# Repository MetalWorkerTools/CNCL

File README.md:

# CNCL
[CNCL](https://www.microsoft.com/store/apps/9P42TB5T697H), a conversational lathe application, gives a CNC controlled conventional lathe the ability to perform CNC tasks without CNC programming or the need for a CAD or CAM program. [CNCL](https://www.microsoft.com/store/apps/9P42TB5T697H) makes it easy to precisely turn a radius or a taper, grind drills and mills, broach a gear, knurl (cut) a shaft, do any pitch (high precision) threading or rigid tapping, turn a spur gear or pulley cutter, mill a helix gear, simply by setting a few parameters. No complex calculations needed, all you need are the dimensions of the part to turn. The built-in tool change and tool library let you select a tool and continue without the need for adjusting positions. Change from Metric to Inches by a click on a button. Backlash compensation is implemented, no need to fit ball screws. For repetitive tasks, a record and play-back function is available. The recorded GCodes can be saved for use on other types of controllers. A manual is built-in and can be printed.  
[CNCL](https://www.microsoft.com/store/apps/9P42TB5T697H) is optimized to run on a small 10" touch screen (tablet). The supported controllers are [GRBL](https://github.com/gnea/grbl/wiki), [GRBL-L](https://github.com/MetalWorkerTools/grbl-L), [GRBL-L-Mega](https://github.com/MetalWorkerTools/grbl-L-Mega),  [uCNC](https://github.com/Paciente8159/uCNC/wiki), [grblHAL](https://github.com/grblHAL/core/wiki), [FluidNC](http://wiki.fluidnc.com/en/home), [Grbl_ESP32](https://github.com/bdring/Grbl_Esp32/wiki) or compatibles, free open source controllers based on affordable (Arduino) hardware. Check the [hardware compatibility list](https://github.com/MetalWorkerTools/CNCL/wiki/Hardware-Compatibility-List) for more information. The controller can be connected by USB, Bluetooth or a (Wi-Fi) network.  
If you ever wanted to start with CNC, this is the easy and affordable way to do it.
[CNCL](https://www.microsoft.com/store/apps/9P42TB5T697H) is also provided as a 30 days trial version. The trial version is a full version without limitations. Check the License Information task for more information.  
[CNCL](https://www.microsoft.com/store/apps/9P42TB5T697H) is available from the Microsoft Store.  

Thinking about a CNC rotary table, checkout [CNCR](https://www.microsoft.com/store/apps/9N7HPG47XK0G) from the Microsoft store..
<p>&nbsp;</p> 

## For more information, read the [WiKi](https://github.com/MetalWorkerTools/CNCL/wiki)
## Version [2.4.1](https://github.com/MetalWorkerTools/CNCL/wiki/Version-Information) is released on 10-2026.
## Use [**Issues**](https://github.com/MetalWorkerTools/CNCL/issues) to report a bug or request a feature

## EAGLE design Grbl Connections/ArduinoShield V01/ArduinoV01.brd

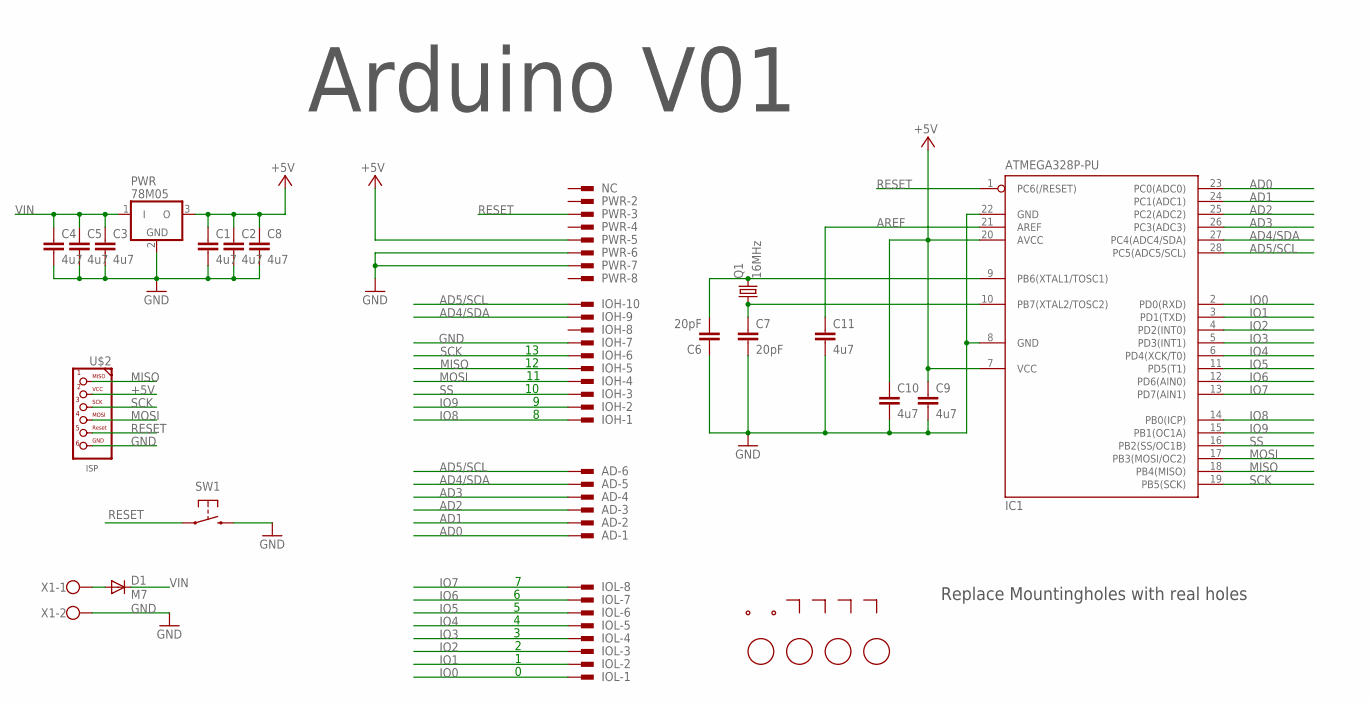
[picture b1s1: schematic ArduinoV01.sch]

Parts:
AD-1, AD-2, AD-3, AD-4, AD-5, AD-6: PINHD-1X1; 1X01
C1, C2, C3, C4, C5, C8, C9, C10, C11: 4u7; C0805
C6, C7: 20pF; C0805
D1: M7; DO214AC
FD1, FD2, FD3, FD4: FIDUCIALMOUNT; FIDUCIA-MOUNT
IC1: ATMEGA328P-PU; DIL28-3
IOH-1, IOH-2, IOH-3, IOH-4, IOH-5, IOH-6, IOH-7, IOH-8, IOH-9, IOH-10: PINHD-1X1; 1X01
IOL-1, IOL-2, IOL-3, IOL-4, IOL-5, IOL-6, IOL-7, IOL-8: PINHD-1X1; 1X01
NC: PINHD-1X1; 1X01
PWR: 78M05; DPACK
PWR-2, PWR-3, PWR-4, PWR-5, PWR-6, PWR-7, PWR-8: PINHD-1X1; 1X01
Q1: 16MHz; HC49/S
SW1: SWITCH1X2; SW8X4-SMD
U$1: MARKERDUAL-90; MARKER90
U$2: ISPE; 2X03EDGE
U$3, U$4, U$5, U$6: MARKER
X1: SCREWTERMINATOR1X2V; W237-102V

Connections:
+5V: C1.1, C2.1, C8.1, C9.1, C10.1, IC1.7 (VCC), IC1.20 (AVCC), PWR.3 (O), PWR-5.1, U$2.P$2 (2)
AD0: AD-1.1, IC1.23 (PC0(ADC0))
AD1: AD-2.1, IC1.24 (PC1(ADC1))
AD2: AD-3.1, IC1.25 (PC2(ADC2))
AD3: AD-4.1, IC1.26 (PC3(ADC3))
AD4/SDA: AD-5.1, IC1.27 (PC4(ADC4/SDA)), IOH-9.1
AD5/SCL: AD-6.1, IC1.28 (PC5(ADC5/SCL)), IOH-10.1
AREF: C11.1, IC1.21 (AREF)
GND: C1.2, C2.2, C3.2, C4.2, C5.2, C6.1, C7.2, C8.2, C9.2, C10.2, C11.2, IC1.8 (GND), IC1.22 (GND), IOH-7.1, PWR.2 (GND), PWR-6.1, PWR-7.1, SW1.2 (S), U$2.P$6 (6), X1.2
IO0: IC1.2 (PD0(RXD)), IOL-1.1
IO1: IC1.3 (PD1(TXD)), IOL-2.1
IO2: IC1.4 (PD2(INT0)), IOL-3.1
IO3: IC1.5 (PD3(INT1)), IOL-4.1
IO4: IC1.6 (PD4(XCK/T0)), IOL-5.1
IO5: IC1.11 (PD5(T1)), IOL-6.1
IO6: IC1.12 (PD6(AIN0)), IOL-7.1
IO7: IC1.13 (PD7(AIN1)), IOL-8.1
IO8: IC1.14 (PB0(ICP)), IOH-1.1
IO9: IC1.15 (PB1(OC1A)), IOH-2.1
MISO: IC1.18 (PB4(MISO)), IOH-5.1, U$2.P$1 (1)
MOSI: IC1.17 (PB3(MOSI/OC2)), IOH-4.1, U$2.P$4 (4)
unnamed: C6.2, IC1.9 (PB6(XTAL1/TOSC1)), Q1.2
unnamed: C7.1, IC1.10 (PB7(XTAL2/TOSC2)), Q1.1
unnamed: D1.A, X1.1
RESET: IC1.1 (PC6(/RESET)), PWR-3.1, SW1.1, U$2.P$5 (5)
SCK: IC1.19 (PB5(SCK)), IOH-6.1, U$2.P$3 (3)
SS: IC1.16 (PB2(SS/OC1B)), IOH-3.1
VIN: C3.1, C4.1, C5.1, D1.C, PWR.1 (I)

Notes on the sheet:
Arduino V01
Replace Mountingholes with real holes

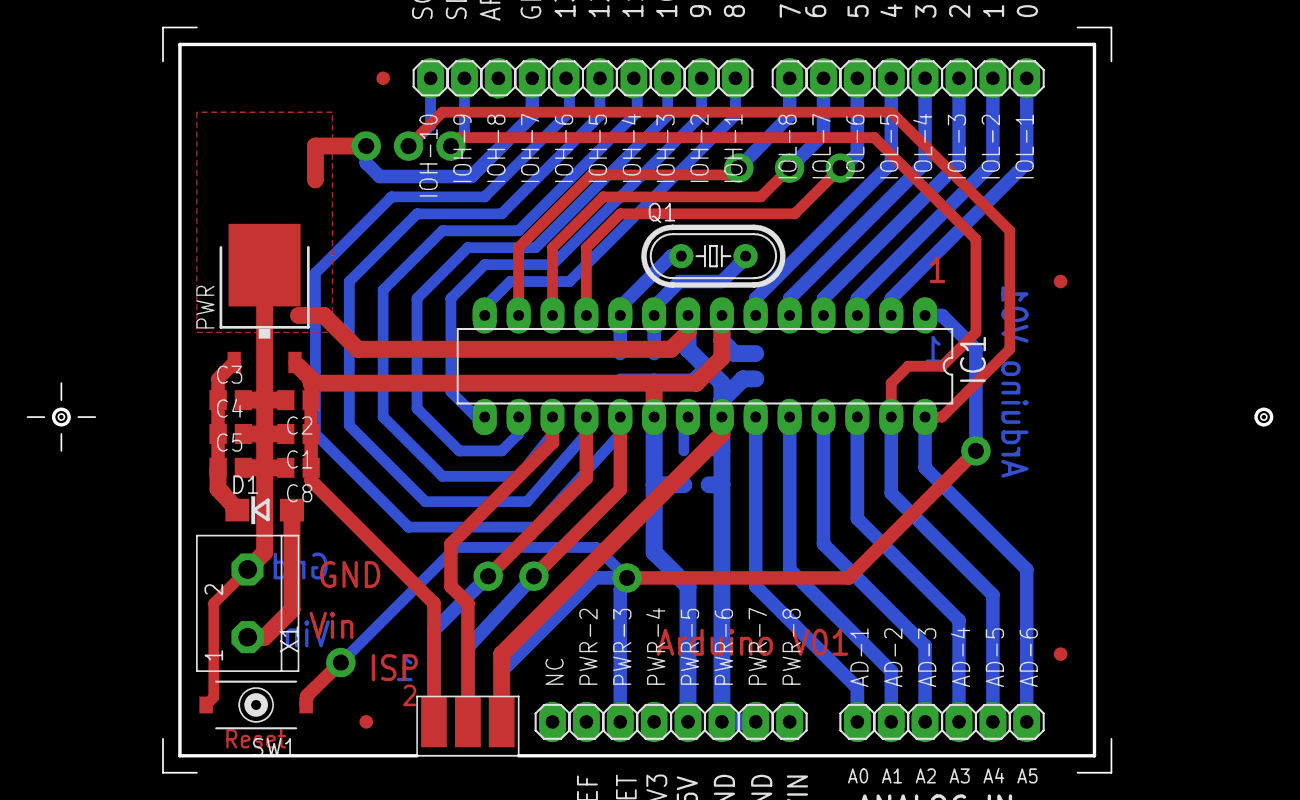
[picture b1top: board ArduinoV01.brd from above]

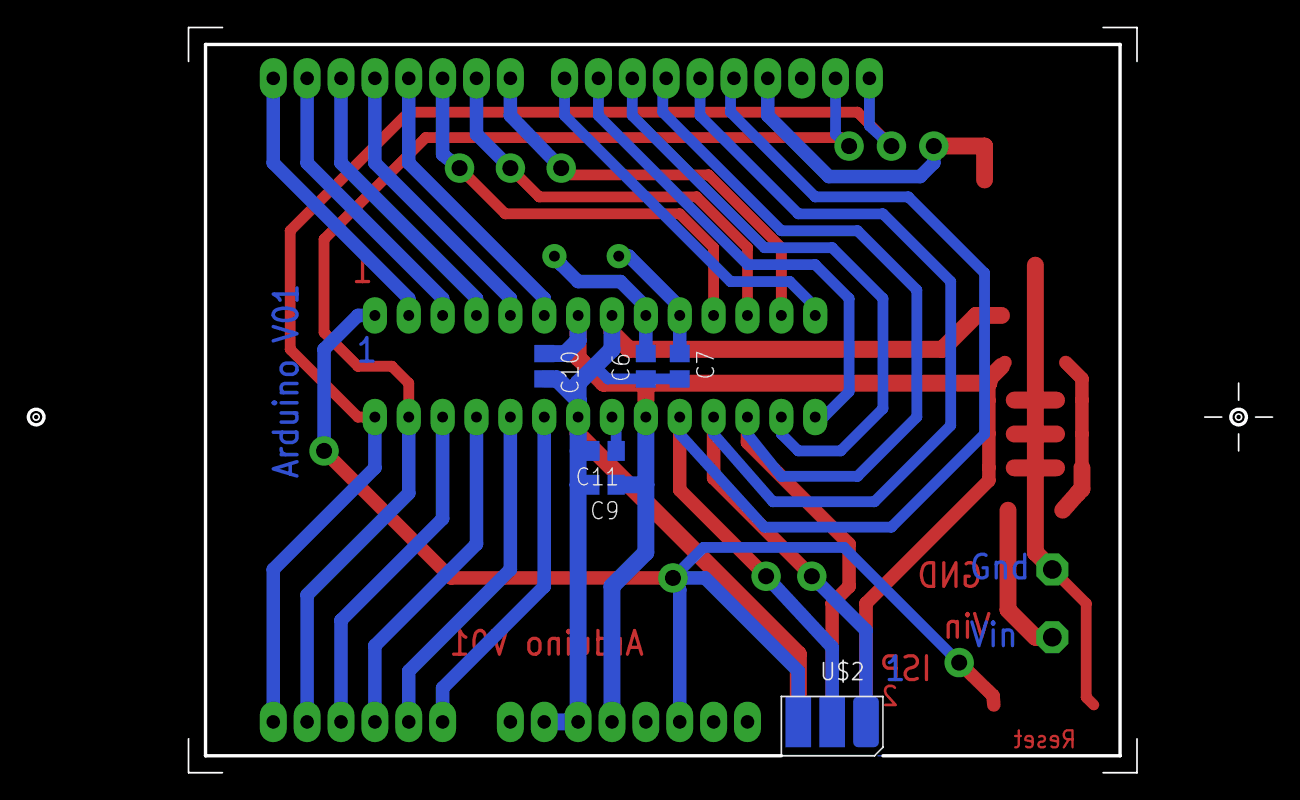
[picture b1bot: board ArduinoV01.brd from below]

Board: 2 copper layers, 93.2 x 55.8 mm, 59 parts (6 on the bottom side), 28 nets.

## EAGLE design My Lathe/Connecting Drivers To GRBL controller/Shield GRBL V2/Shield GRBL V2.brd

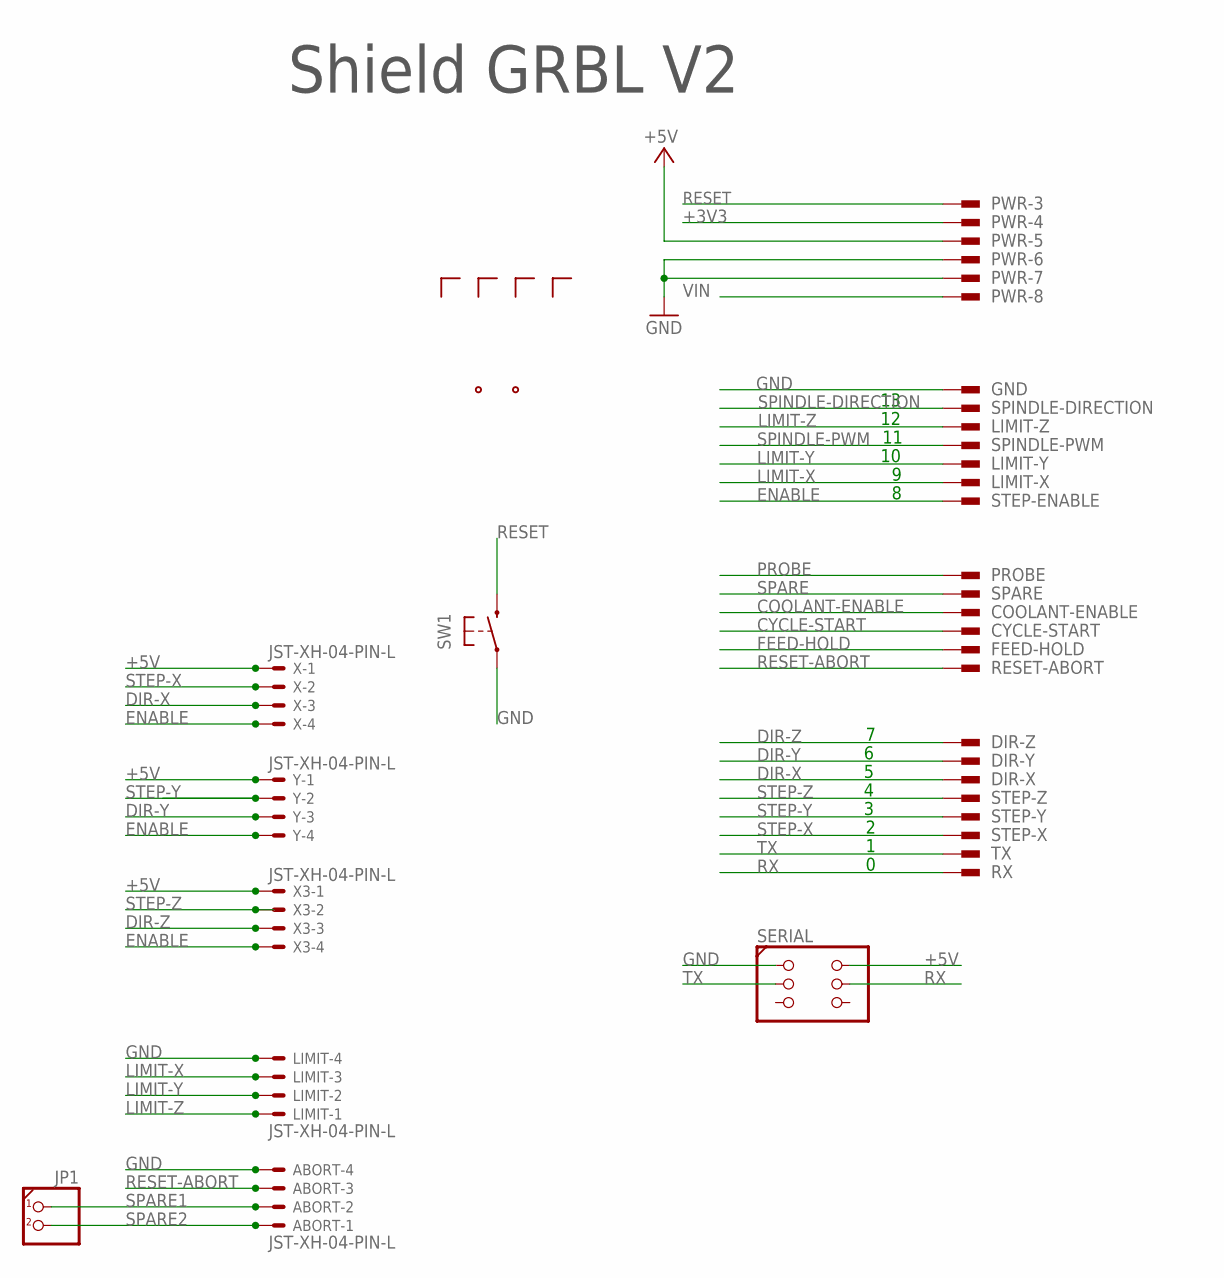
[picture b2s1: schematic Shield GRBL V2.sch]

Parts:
ABORT: JST-XH-04-PIN-L; JST-XH-04-PACKAGE-LONG-PAD
COOLANT-ENABLE: PINHD-1X1; 1X01
CYCLE-START: PINHD-1X1; 1X01
DIR-X: PINHD-1X1; 1X01
DIR-Y: PINHD-1X1; 1X01
DIR-Z: PINHD-1X1; 1X01
FEED-HOLD: PINHD-1X1; 1X01
GND: PINHD-1X1; 1X01
JP1: PINHD-1X2; 1X02
LIMIT: JST-XH-04-PIN-L; JST-XH-04-PACKAGE-LONG-PAD
LIMIT-X: PINHD-1X1; 1X01
LIMIT-Y: PINHD-1X1; 1X01
LIMIT-Z: PINHD-1X1; 1X01
PROBE: PINHD-1X1; 1X01
PWR-3, PWR-4, PWR-5, PWR-6, PWR-7, PWR-8: PINHD-1X1; 1X01
RESET-ABORT: PINHD-1X1; 1X01
RX: PINHD-1X1; 1X01
SERIAL: 3x2 M; 2X03S
SPARE: PINHD-1X1; 1X01
SPINDLE-DIRECTION: PINHD-1X1; 1X01
SPINDLE-PWM: PINHD-1X1; 1X01
STEP-ENABLE: PINHD-1X1; 1X01
STEP-X: PINHD-1X1; 1X01
STEP-Y: PINHD-1X1; 1X01
STEP-Z: PINHD-1X1; 1X01
SW1: SWITCH1X2; SW8X4-SMD
TX: PINHD-1X1; 1X01
U$1: MARKERDUAL-60; MARKER60
U$2, U$3, U$4, U$5: MARKER
X, X3: JST-XH-04-PIN-L; JST-XH-04-PACKAGE-LONG-PAD
Y: JST-XH-04-PIN-L; JST-XH-04-PACKAGE-LONG-PAD

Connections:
+3V3: PWR-4.1
+5V: PWR-5.1, SERIAL.2, X.1, X3.1, Y.1
COOLANT-ENABLE: COOLANT-ENABLE.1
CYCLE-START: CYCLE-START.1
DIR-X: DIR-X.1, X.3
DIR-Y: DIR-Y.1, Y.3
DIR-Z: DIR-Z.1, X3.3
ENABLE: STEP-ENABLE.1, X.4, X3.4, Y.4
FEED-HOLD: FEED-HOLD.1
GND: ABORT.4, GND.1, LIMIT.4, PWR-6.1, PWR-7.1, SERIAL.1, SW1.1
LIMIT-X: LIMIT.3, LIMIT-X.1
LIMIT-Y: LIMIT.2, LIMIT-Y.1
LIMIT-Z: LIMIT.1, LIMIT-Z.1
PROBE: PROBE.1
RESET: PWR-3.1, SW1.2 (S)
RESET-ABORT: ABORT.3, RESET-ABORT.1
RX: RX.1, SERIAL.4
SPARE: SPARE.1
SPARE1: ABORT.2, JP1.1
SPARE2: ABORT.1, JP1.2
SPINDLE-DIRECTION: SPINDLE-DIRECTION.1
SPINDLE-PWM: SPINDLE-PWM.1
STEP-X: STEP-X.1, X.2
STEP-Y: STEP-Y.1, Y.2
STEP-Z: STEP-Z.1, X3.2
TX: SERIAL.3, TX.1
VIN: PWR-8.1

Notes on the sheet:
Shield GRBL V2

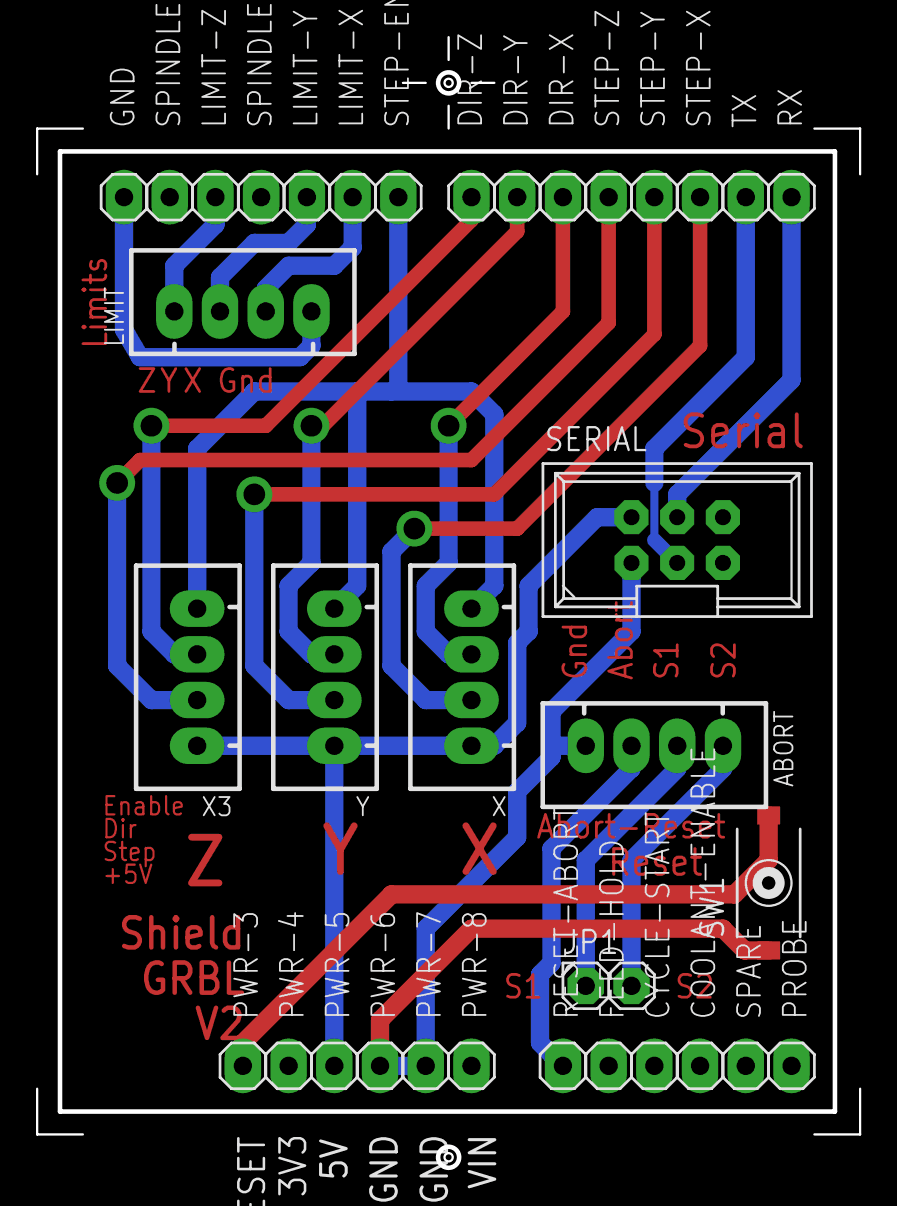
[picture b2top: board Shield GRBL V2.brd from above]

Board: 2 copper layers, 45.6 x 62.8 mm, 40 parts (1 on the bottom side), 18 nets.

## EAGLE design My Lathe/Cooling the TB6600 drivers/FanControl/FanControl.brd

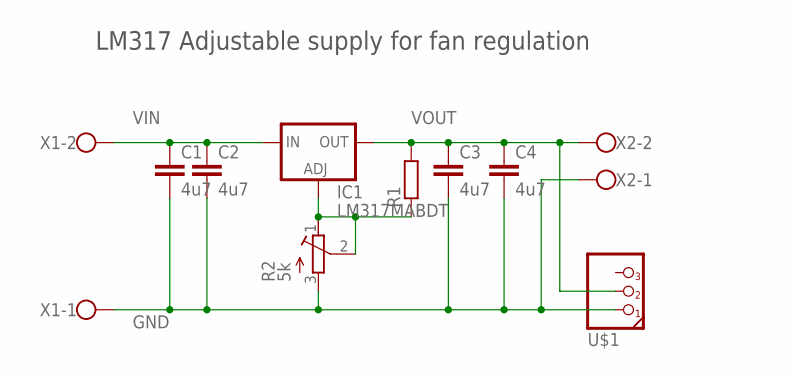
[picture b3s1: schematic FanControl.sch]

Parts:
C1, C2, C3, C4: 4u7; C0805
IC1: LM317MABDT; DPACK
R1: R-EU_R1206; R1206
R2: 5k; RTRIMT93YA
U$1: PINHD-1X3; 1X03
X1, X2: SCREWTERMINATOR1X2; W237-102

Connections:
GND: C1.2, C2.2, C3.2, C4.2, R2.3 (A), U$1.1, X1.1, X2.1
unnamed: IC1.1 (ADJ), R1.1, R2.1 (E), R2.2 (S)
VIN: C1.1, C2.1, IC1.3 (IN), X1.2
VOUT: C3.1, C4.1, IC1.4 (OUT), R1.2, U$1.2, X2.2

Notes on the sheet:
LM317 Adjustable supply for fan regulation

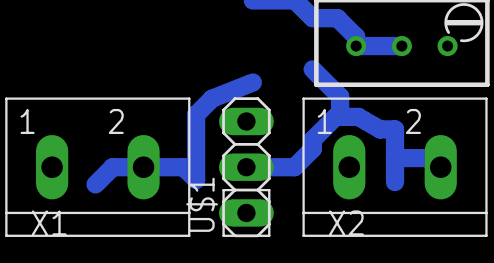
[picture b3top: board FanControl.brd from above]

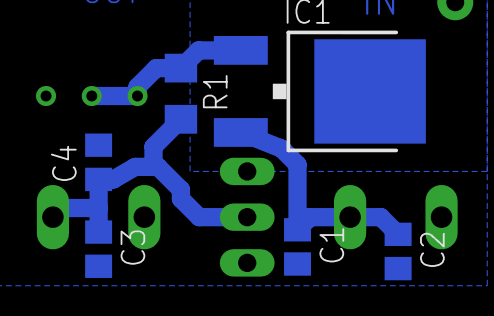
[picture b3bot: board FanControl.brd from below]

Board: 2 copper layers, 10 parts (6 on the bottom side), 4 nets.

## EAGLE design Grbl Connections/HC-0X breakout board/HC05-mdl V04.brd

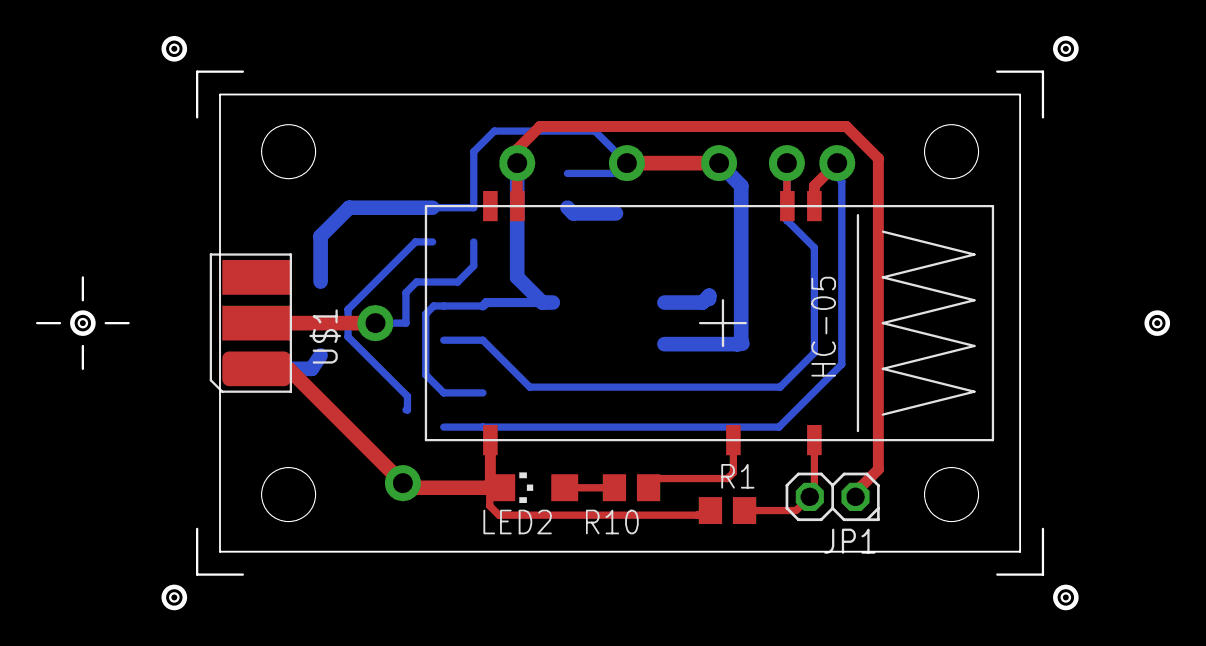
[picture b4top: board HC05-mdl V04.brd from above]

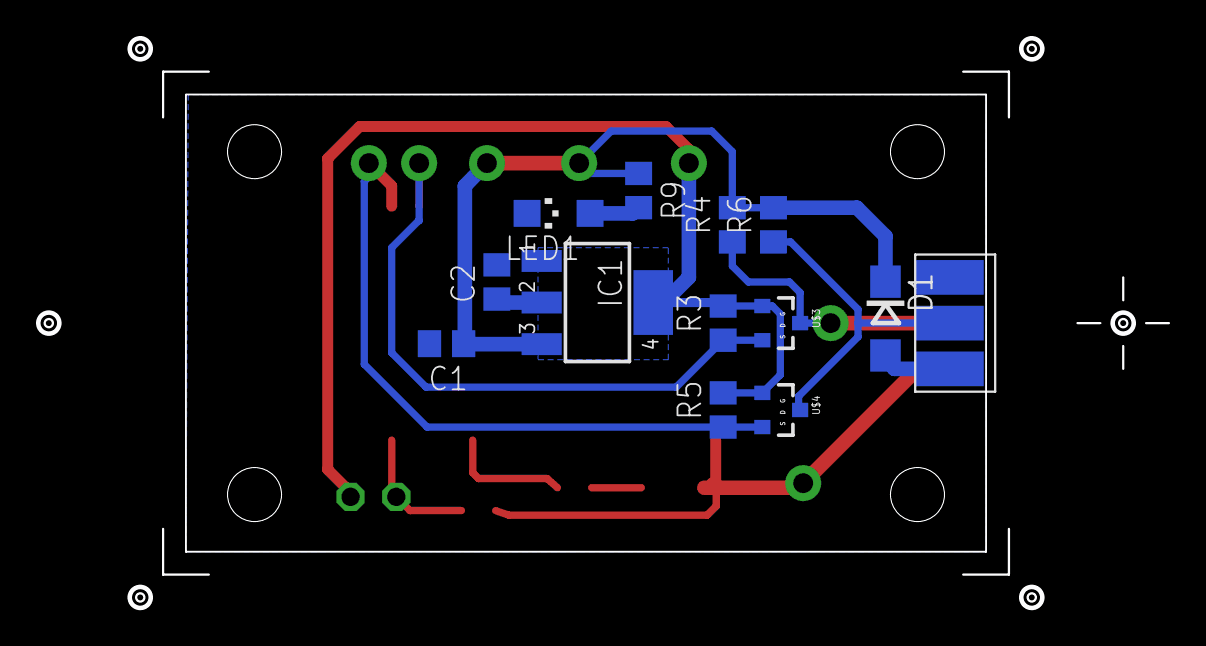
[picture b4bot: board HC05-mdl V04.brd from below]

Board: 2 copper layers, 62.8 x 31.6 mm, 23 parts (12 on the bottom side), 12 nets.

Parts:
C1: 4U7; C0805
C2: 4u7; C0805
D1: SS16; DO214AC
IC1: AMS-1117-3V3; SOT223
JP1: PINHD-1X2; 1X02
LED1: Green; CHIPLED_1206
LED2: red; CHIPLED_1206
R1, R3, R4, R5, R6: 10k; R0805
R9: 2K2; R0805
R10: 470; R0805
U$1: PINHD-2X3EDGE; 2X03EDGE
U$2, U$5, U$8, U$9: MARKER
U$3, U$4: 2N7002-S; SOT23-FET-SMALL
U$6: MARKERDUAL-60; MARKER60
U$7: HC-05-MIN; HC-05-MIN-SMD

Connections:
+3V3: C2.1, IC1.2, IC1.4, JP1.1, R3.2, R5.2, U$3.G, U$4.G, U$7.3V3
+5V: D1.A, U$1.P$2
GND: C1.2, C2.2, IC1.1, LED1.C, LED2.C, R1.1, U$1.P$1, U$7.GND2
KEY_L: JP1.2, R1.2, U$7.KEY
LED: R10.1, U$7.LED
unnamed: LED1.A, R9.2
unnamed: LED2.A, R10.2
RXD_H: R4.1, U$1.P$3, U$3.D
RXD_L: R3.1, U$3.S, U$7.RX
TXD_H: R6.1, U$1.P$4, U$4.D
TXD_L: R5.1, U$4.S, U$7.TX
VCC: C1.1, D1.C, IC1.3, R4.2, R6.2, R9.1

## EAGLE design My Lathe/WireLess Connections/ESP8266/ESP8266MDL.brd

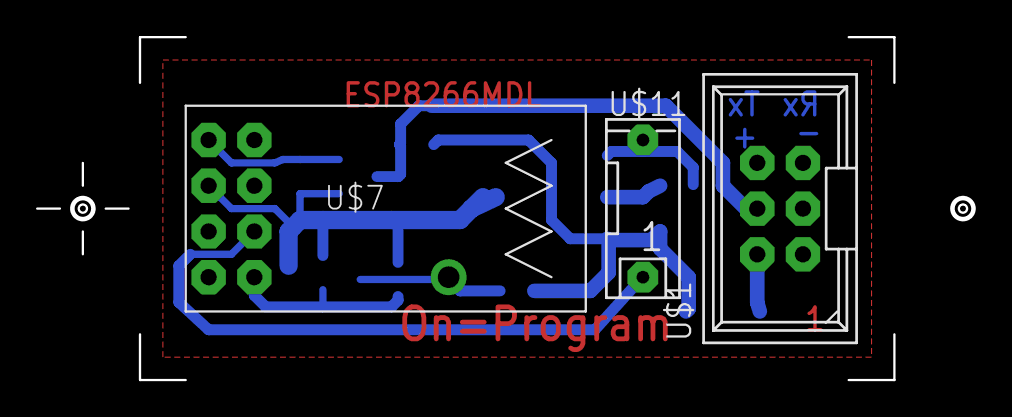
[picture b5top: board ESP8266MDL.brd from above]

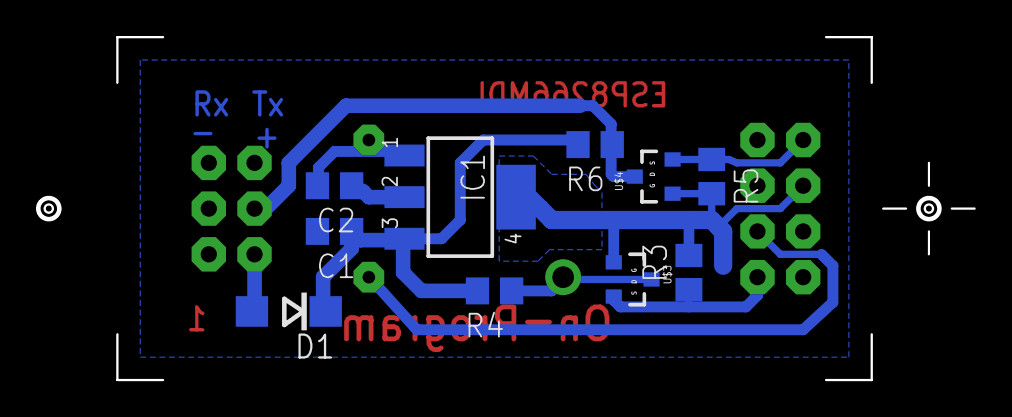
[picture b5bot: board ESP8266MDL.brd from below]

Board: 2 copper layers, 52.0 x 18.9 mm, 18 parts (10 on the bottom side), 9 nets.

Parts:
C1: 4U7; C0805
C2: 4u7; C0805
D1: SS16; DO214AC
IC1: AMS-1117-3V3; SOT223
R3, R4, R5, R6: 10k; R0805
U$1: PINHD-2X3S; 2X03S
U$2, U$5, U$8, U$9: MARKER
U$3, U$4: 2N7002-S; SOT23-FET-SMALL
U$6: MARKERDUAL-50; MARKER50
U$7: ESP8266
U$11: DP01-DIL; DP-01

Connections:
+3V3: C2.1, IC1.2, IC1.4, R3.2, R5.2, U$3.G, U$4.G, U$7.P$4, U$7.P$8
+5V: D1.A, U$1.2
GND: C1.2, C2.2, IC1.1, U$1.1, U$7.P$1, U$11.P$1
GPIO0: U$7.P$5, U$11.P$2
RXD_H: R4.1, U$1.3, U$3.D
RXD_L: R3.1, U$3.S, U$7.P$7
TXD_H: R6.1, U$1.4, U$4.D
TXD_L: R5.1, U$4.S, U$7.P$2
VCC: C1.1, D1.C, IC1.3, R4.2, R6.2

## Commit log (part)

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2020-12-24 Update issue templates
2020-12-30 Updated My Lathe files
2021-01-02 grbl wireless connections
    Added documentation, boards and firmware for grbl WiFi and bluetooth connections
2021-01-02 Update eagle files
2021-06-01 Release version 2.3.71 06-2021
2021-06-01 Release 2.3.71
2021-10-19 Release 2.3.73 on 08-2021
2022-01-11 release 2.3.77
2022-03-31 release 2.3.83
2022-03-31 release 2.3.81
2022-05-20 Added photo's
2022-05-20 Cleanup
2022-06-20 Added the quick change tool post drawing
2022-12-02 Add files via upload
    Added dwg files for the modification that uses 2 bearings to keep the saddle pressed to the lathe bed
2022-12-23 release 2.3.85
2023-05-19 Release 2.3.87
2023-08-14 Release 2.3.93
2024-05-04 Release 2.3.95 05-2024
2025-03-05 Version 2.3.97 released on 03 2025
2025-11-15 Release of version 2.3.99 on 11-2025
2025-11-27 Release of version 2.3.101 with spindle speed control (M3,M5) and constant surface speed.
2025-12-14 Added pictures to show the C-axis mount
2026-01-08 Release of version 2.3.101 on 01-2026
